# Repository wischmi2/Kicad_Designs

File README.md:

# Kicad_Designs

nRF54L15 sensor nodes (feather + one CN1 sensor board per node), the pouch gateway, and tools.
Layout since 2026-11-10 (old -> new map: `docs\reorg_2026-11-10.md`). Every board folder has a STATUS.md; read it first.

```
hardware\
  feather\              nRF54L15 feather, main board (KiCad project in feather\nrf54l15_feather\)
  sensors\              CN1 sensor boards + CN1_SENSOR_CONNECTOR.md, SENSORS.md (SENS_ID register)
    template\ ph\ orp\ dissolved_oxygen\ conductivity\ water_level\ water_level_tc2030\
  gateway\              pouch gateway (docs\ inside)
  prog_adapter\         programming adapter (XM125 UART, TC2030 SWD, USB-C 3.0 V)
  archive\              old/paused boards: nrf54l15_v2, v3, v4, ph_sensor, xiao_breakout,
                        pcbway_production, soil_moisture (the old root-level project)
firmware\
  boards\               Zephyr board definitions (firmware\ is BOARD_ROOT)
  apps\feather_node\    node application, build/flash scripts
mechanical\             enclosure exports: tidemark, ledger, crown, probe_nodes, bench_tray,
                        concepts\<product>, hardware_lists
docs\                   cross-board notes, datasheets, sourcing, cost analysis
CLAUDE.md               coordinator instructions and status log
```

Per board: `sourcing\` holds BOMs and part notes, `docs\` holds renders and design notes,
`archive\` / `fab_<date>\` hold fab output. KiCad project files keep their original names.
Board STEP and fab-zip handoffs live outside the repo in `C:\Personal-Agents\shared\handoff\<board>\`.

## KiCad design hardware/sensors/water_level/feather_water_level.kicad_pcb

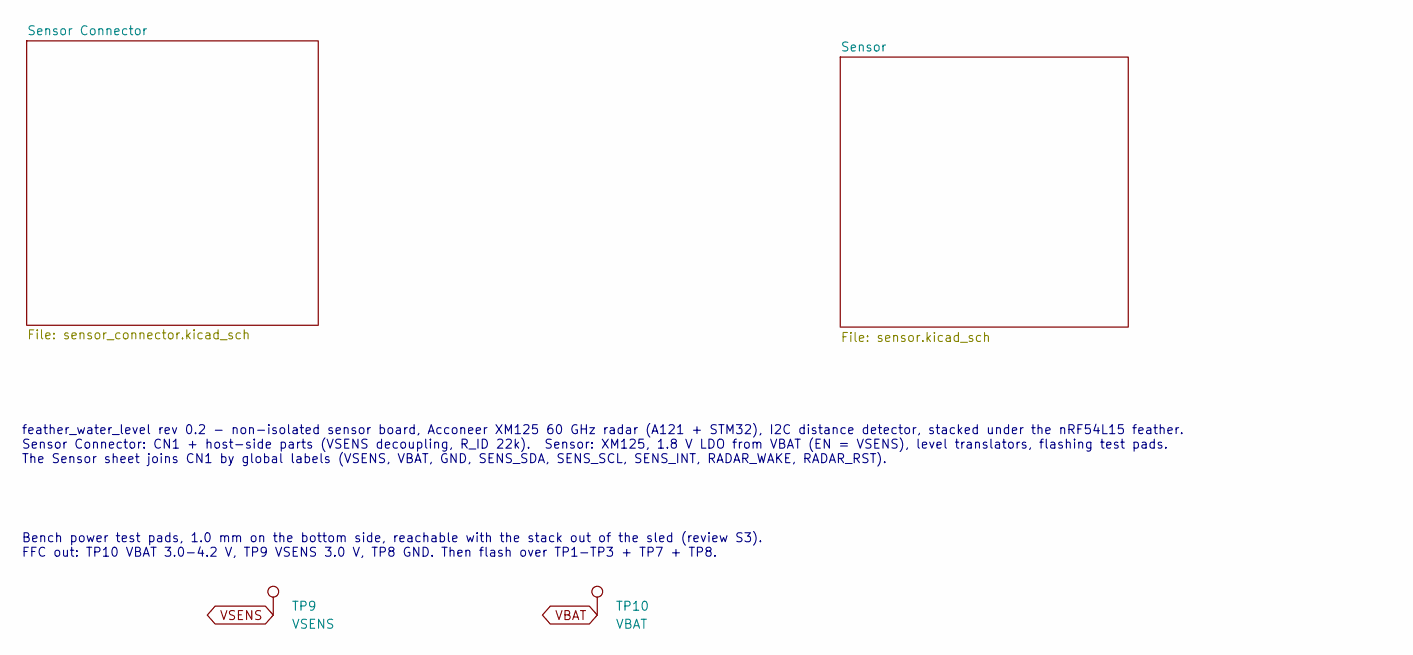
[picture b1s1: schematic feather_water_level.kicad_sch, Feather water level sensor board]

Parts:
TP9: VSENS; TestPoint_Pad_D1.0mm; MPN DNP (test pad)
TP10: VBAT; TestPoint_Pad_D1.0mm; MPN DNP (test pad)

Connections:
VBAT: TP10.1; also elsewhere on the board
VSENS: TP9.1; also elsewhere on the board

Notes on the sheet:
feather_water_level rev 0.2 - non-isolated sensor board, Acconeer XM125 60 GHz radar (A121 + STM32), I2C distance detector, stacked under the nRF54L15 feather. Sensor Connector: CN1 + host-side parts (VSENS decoupling, R_ID 22k). Sensor: XM125, 1.8 V LDO from VBAT (EN = VSENS), level translators, f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
Bench power test pads, 1.0 mm on the bottom side, reachable with the stack out of the sled (review S3). FFC out: TP10 VBAT 3.0-4.2 V, TP9 VSENS 3.0 V, TP8 GND. Then flash over TP1-TP3 + TP7 + TP8.

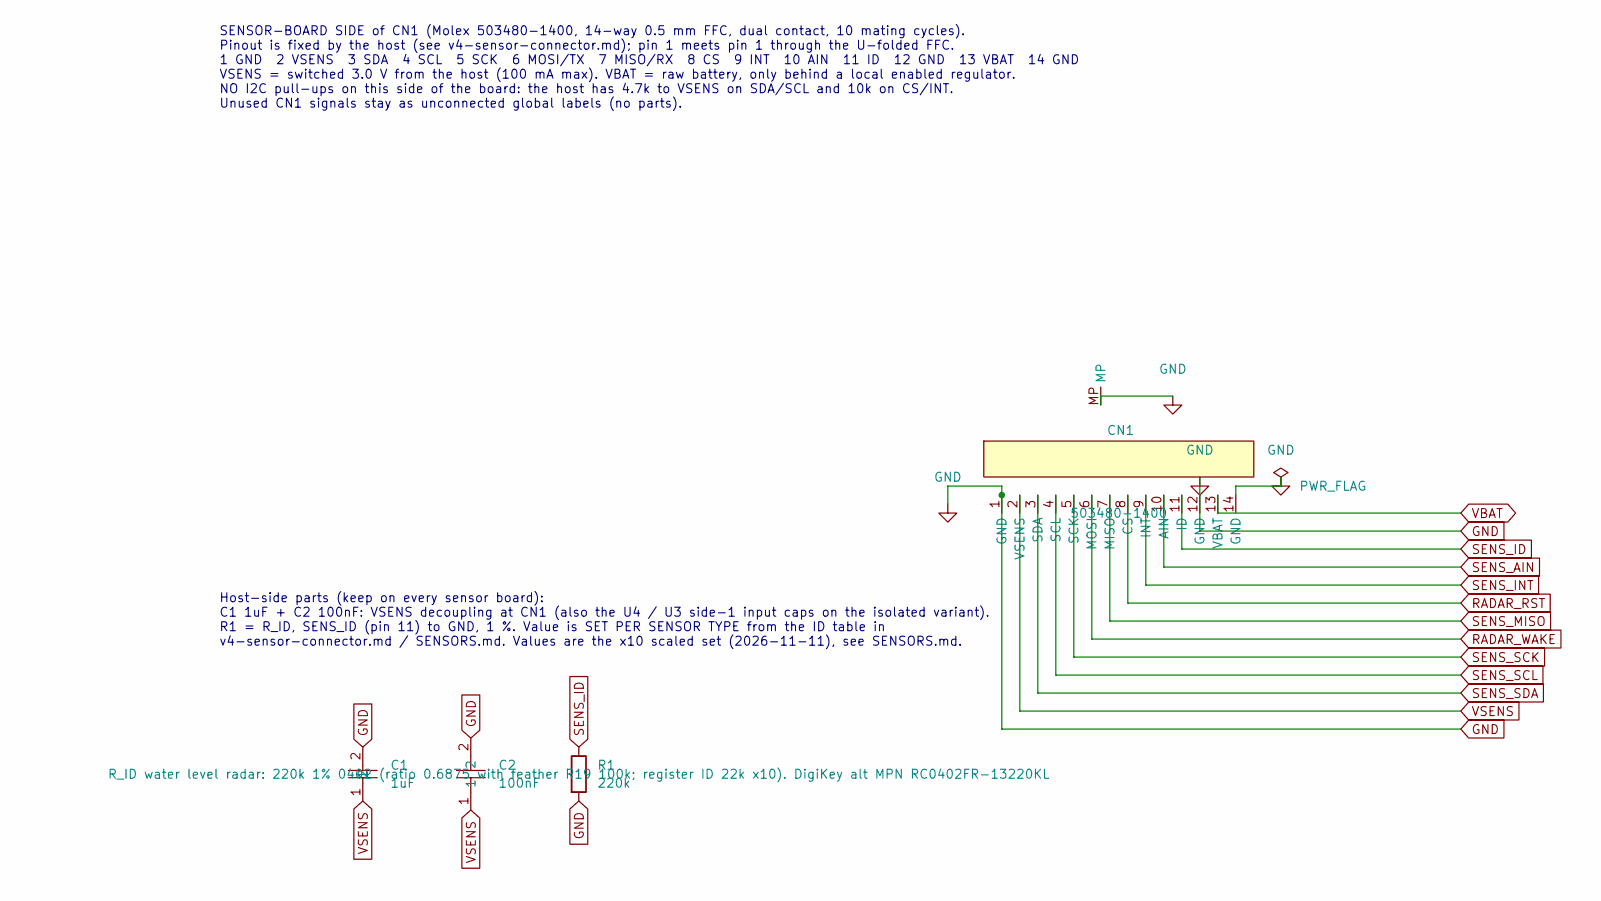
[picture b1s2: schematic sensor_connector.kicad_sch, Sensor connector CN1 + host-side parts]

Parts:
C1: 1uF; C0402; MPN CL05A105KO5NNNC; LCSC Part C29266
C2: 100nF; C0603; MPN CC0603KRX7R9BB104; LCSC Part C14663
CN1: 503480-1400; Molex_503480-1400_1x14-1MP_P0.50mm_Horizontal; MPN 503480-1400
R1: 220k; R0402; Tolerance 1%; MPN RC0402FR-07220KL

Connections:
GND: C1.2, C2.2, CN1.1 (GND), CN1.12 (GND), CN1.14 (GND), CN1.MP, R1.2; also elsewhere on the board
RADAR_RST: CN1.8 (CS); also elsewhere on the board
RADAR_WAKE: CN1.6 (MOSI); also elsewhere on the board
SENS_AIN: CN1.10 (AIN)
SENS_ID: CN1.11 (ID), R1.1
SENS_INT: CN1.9 (INT); also elsewhere on the board
SENS_MISO: CN1.7 (MISO)
SENS_SCK: CN1.5 (SCK)
SENS_SCL: CN1.4 (SCL); also elsewhere on the board
SENS_SDA: CN1.3 (SDA); also elsewhere on the board
VBAT: CN1.13 (VBAT); also elsewhere on the board
VSENS: C1.1, C2.1, CN1.2 (VSENS); also elsewhere on the board

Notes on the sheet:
SENSOR-BOARD SIDE of CN1 (Molex 503480-1400, 14-way 0.5 mm FFC, dual contact, 10 mating cycles). Pinout is fixed by the host (see v4-sensor-connector.md); pin 1 meets pin 1 through the U-folded FFC. 1 GND 2 VSENS 3 SDA 4 SCL 5 SCK 6 MOSI/TX 7 MISO/RX 8 CS 9 INT 10 AIN 11 ID 12 GND 13 VBAT 14 GND VS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
Host-side parts (keep on every sensor board): C1 1uF + C2 100nF: VSENS decoupling at CN1 (also the U4 / U3 side-1 input caps on the isolated variant). R1 = R_ID, SENS_ID (pin 11) to GND, 1 %. Value is SET PER SENSOR TYPE from the ID table in v4-sensor-connector.md / SENSORS.md. Values are the x10 s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

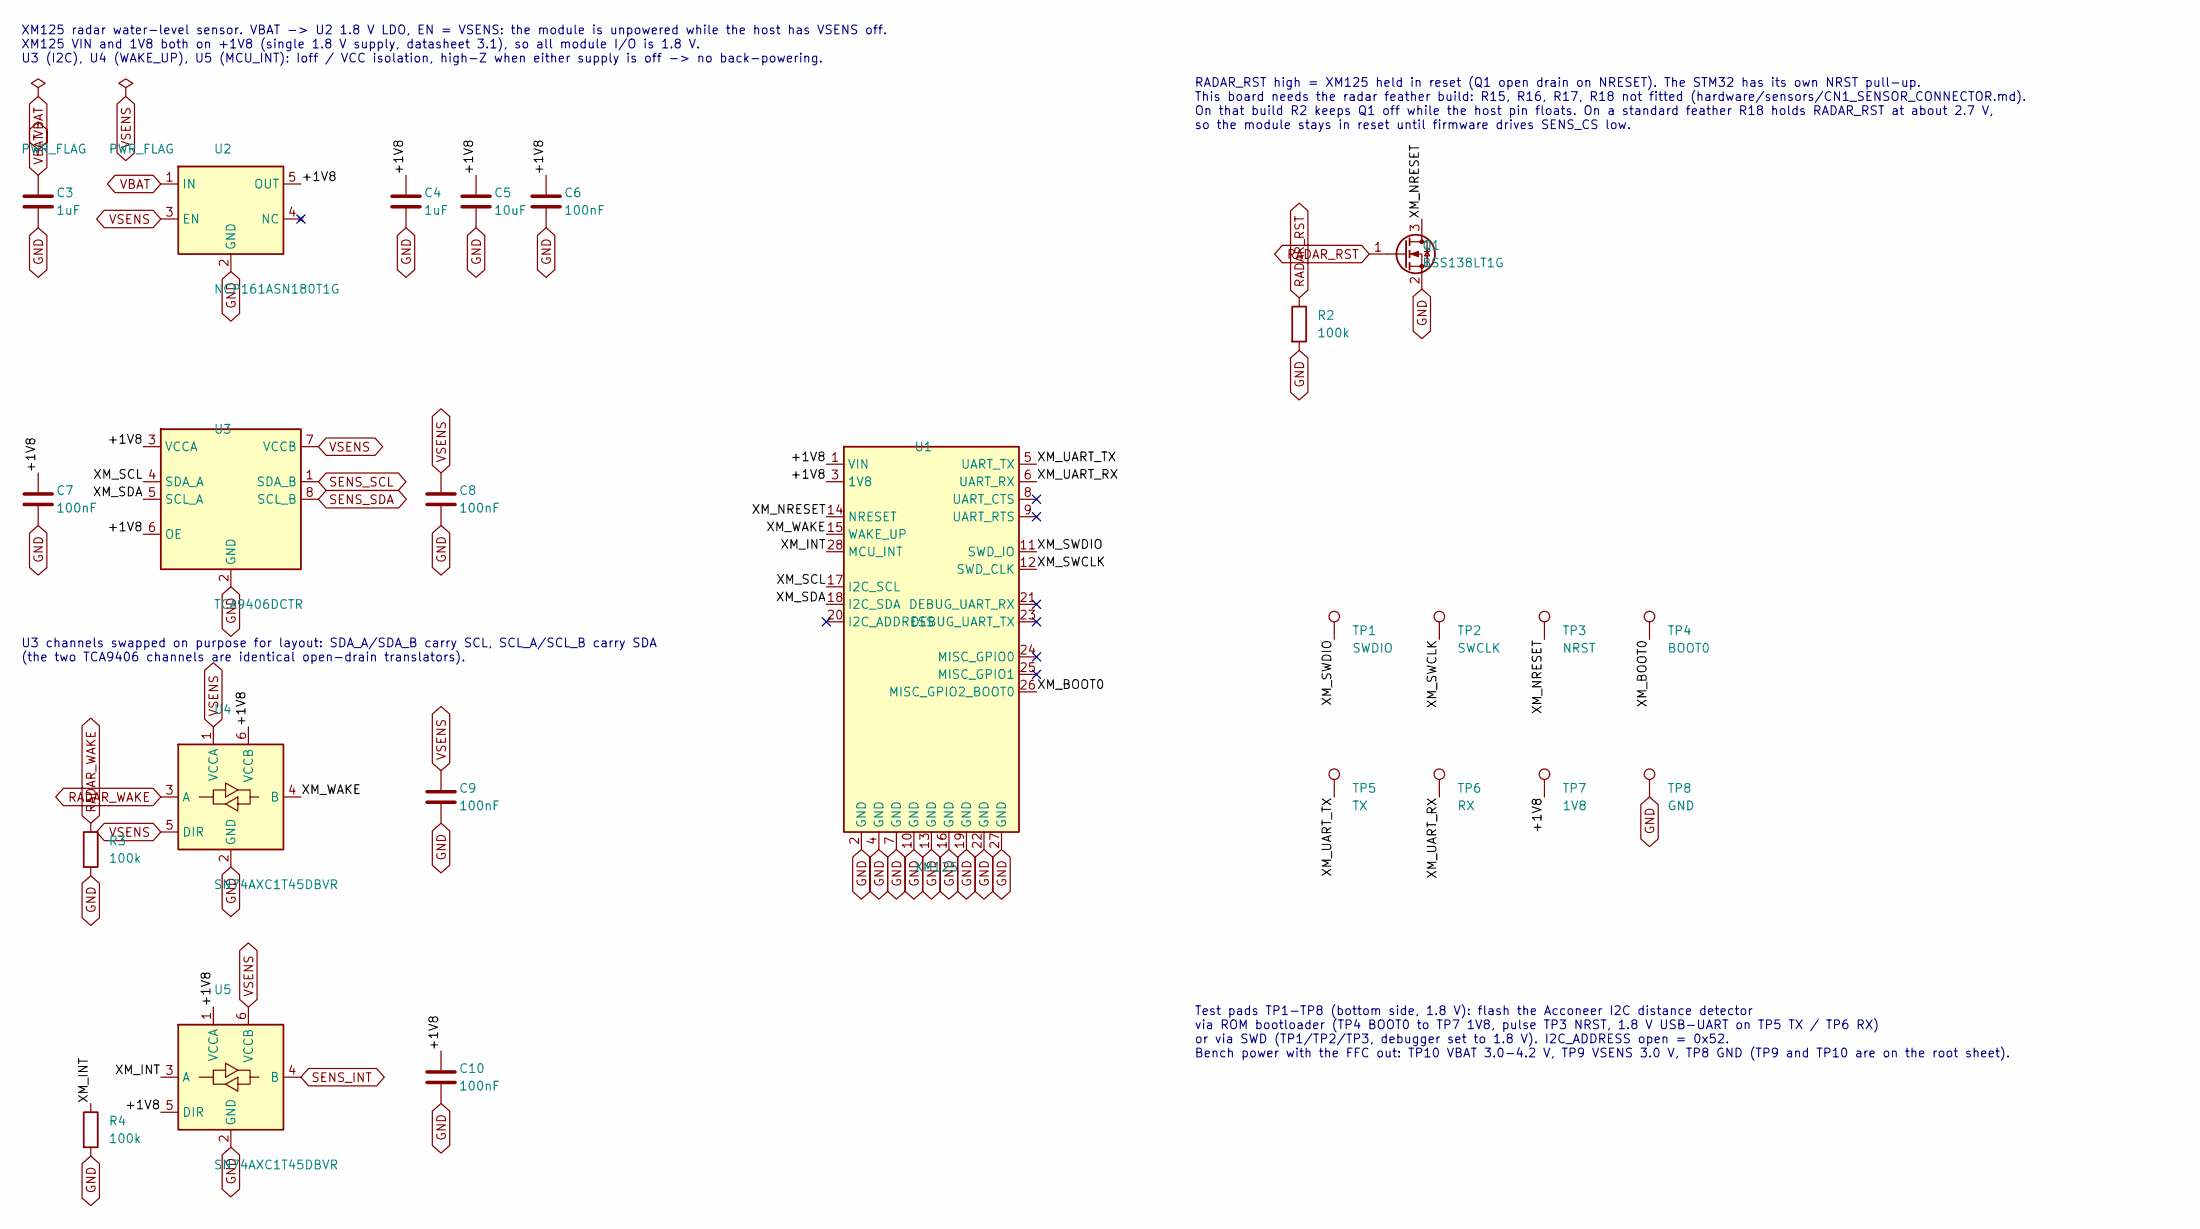
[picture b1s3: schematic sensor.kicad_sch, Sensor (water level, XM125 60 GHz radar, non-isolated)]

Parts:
C3, C4: 1uF; C_0402_1005Metric; Voltage 16V; MPN CL05A105KO5NNNC
C5: 10uF; C_0402_1005Metric; Voltage 6.3V; MPN GRM155R60J106ME15D
C6, C7, C8, C9, C10: 100nF; C_0402_1005Metric; Voltage 10V; MPN GRM155R71A104KA01D
Q1: BSS138LT1G; SOT-23; MPN BSS138LT1G
R2, R3, R4: 100k; R_0402_1005Metric; Tolerance 1%; MPN RC0402FR-07100KL
TP1: SWDIO; TestPoint_Pad_D1.0mm; MPN DNP (test pad)
TP2: SWCLK; TestPoint_Pad_D1.0mm; MPN DNP (test pad)
TP3: NRST; TestPoint_Pad_D1.0mm; MPN DNP (test pad)
TP4: BOOT0; TestPoint_Pad_D1.0mm; MPN DNP (test pad)
TP5: TX; TestPoint_Pad_D1.0mm; MPN DNP (test pad)
TP6: RX; TestPoint_Pad_D1.0mm; MPN DNP (test pad)
TP7: 1V8; TestPoint_Pad_D1.0mm; MPN DNP (test pad)
TP8: GND; TestPoint_Pad_D1.0mm; MPN DNP (test pad)
U1: XM125; Acconeer_XM125; MPN XM125
U2: NCP161ASN180T1G; SOT-23-5; MPN NCP161ASN180T1G
U3: TCA9406DCTR; SSOP-8_2.95x2.8mm_P0.65mm; MPN TCA9406DCTR
U4, U5: SN74AXC1T45DBVR; SOT-23-6; MPN SN74AXC1T45DBVR

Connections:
/Sensor/+1V8: C4.1, C5.1, C6.1, C7.1, C10.1, TP7.1, U1.1 (VIN), U1.3 (1V8), U2.5 (OUT), U3.3 (VCCA), U3.6 (OE), U4.6 (VCCB), U5.1 (VCCA), U5.5 (DIR)
/Sensor/XM_BOOT0: TP4.1, U1.26 (MISC_GPIO2_BOOT0)
/Sensor/XM_INT: R4.1, U1.28 (MCU_INT), U5.3 (A)
/Sensor/XM_NRESET: Q1.3 (D), TP3.1, U1.14 (NRESET)
/Sensor/XM_SCL: U1.17 (I2C_SCL), U3.4 (SDA_A)
/Sensor/XM_SDA: U1.18 (I2C_SDA), U3.5 (SCL_A)
/Sensor/XM_SWCLK: TP2.1, U1.12 (SWD_CLK)
/Sensor/XM_SWDIO: TP1.1, U1.11 (SWD_IO)
/Sensor/XM_UART_RX: TP6.1, U1.6 (UART_RX)
/Sensor/XM_UART_TX: TP5.1, U1.5 (UART_TX)
/Sensor/XM_WAKE: U1.15 (WAKE_UP), U4.4 (B)
GND: C3.2, C4.2, C5.2, C6.2, C7.2, C8.2, C9.2, C10.2, Q1.2 (S), R2.2, R3.2, R4.2, TP8.1, U1.2 (GND), U1.4 (GND), U1.7 (GND), U1.10 (GND), U1.13 (GND), U1.16 (GND), U1.19 (GND), U1.22 (GND), U1.27 (GND), U2.2 (GND), U3.2 (GND), U4.2 (GND), U5.2 (GND); also elsewhere on the board
RADAR_RST: Q1.1 (G), R2.1; also elsewhere on the board
RADAR_WAKE: R3.1, U4.3 (A); also elsewhere on the board
SENS_INT: U5.4 (B); also elsewhere on the board
SENS_SCL: U3.1 (SDA_B); also elsewhere on the board
SENS_SDA: U3.8 (SCL_B); also elsewhere on the board
VBAT: C3.1, U2.1 (IN); also elsewhere on the board
VSENS: C8.1, C9.1, U2.3 (EN), U3.7 (VCCB), U4.1 (VCCA), U4.5 (DIR), U5.6 (VCCB); also elsewhere on the board

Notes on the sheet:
XM125 radar water-level sensor. VBAT -> U2 1.8 V LDO, EN = VSENS: the module is unpowered while the host has VSENS off. XM125 VIN and 1V8 both on +1V8 (single 1.8 V supply, datasheet 3.1), so all module I/O is 1.8 V. U3 (I2C), U4 (WAKE_UP), U5 (MCU_INT): Ioff / VCC isolation, high-Z when either sup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
U3 channels swapped on purpose for layout: SDA_A/SDA_B carry SCL, SCL_A/SCL_B carry SDA (the two TCA9406 channels are identical open-drain translators).
RADAR_RST high = XM125 held in reset (Q1 open drain on NRESET). The STM32 has its own NRST pull-up. This board needs the radar feather build: R15, R16, R17, R18 not fitted (hardware/sensors/CN1_SENSOR_CONNECTOR.md). On that build R2 keeps Q1 off while the host pin floats. On a standard feather R18 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
Test pads TP1-TP8 (bottom side, 1.8 V): flash the Acconeer I2C distance detector via ROM bootloader (TP4 BOOT0 to TP7 1V8, pulse TP3 NRST, 1.8 V USB-UART on TP5 TX / TP6 RX) or via SWD (TP1/TP2/TP3, debugger set to 1.8 V). I2C_ADDRESS open = 0x52. Bench power with the FFC out: TP10 VBAT 3.0-4.2 V, 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

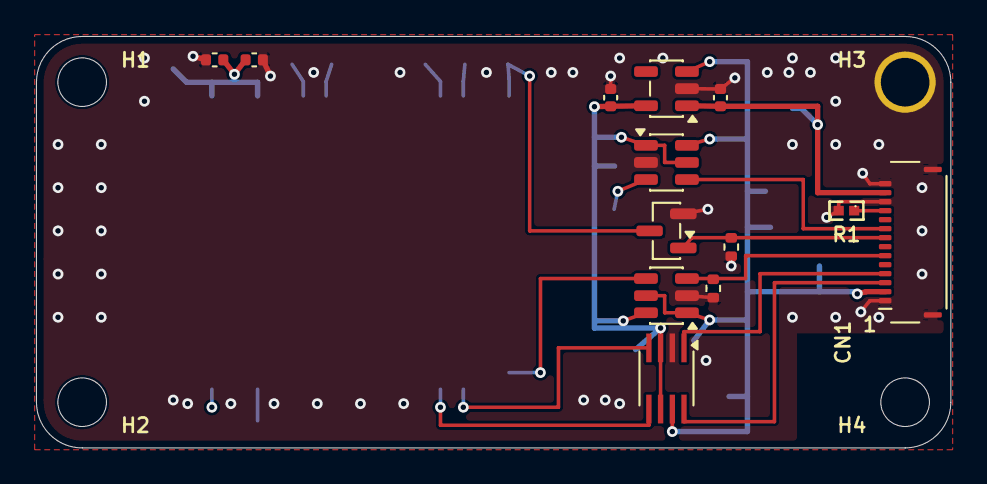
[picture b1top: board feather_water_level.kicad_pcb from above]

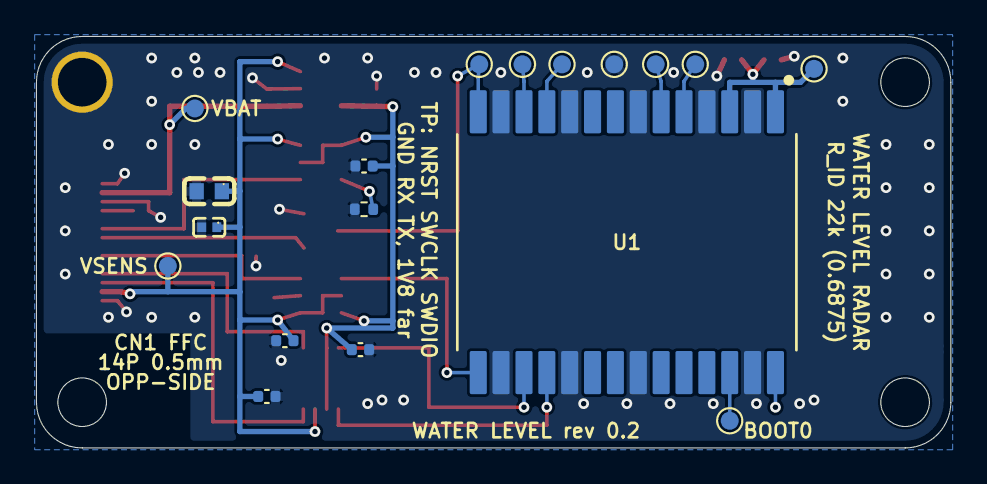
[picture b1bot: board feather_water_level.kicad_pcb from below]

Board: 4 copper layers, 50.8 x 22.9 mm, 35 parts (18 on the bottom side), 20 nets.

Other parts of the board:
H1, H2, H4: M2.5 2.7mm NPTH; MountingHole_2.5mm
H3: M2.5 2.7mm PTH GND; MountingHole_2.5mm_Pad

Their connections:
GND: H3.1; also elsewhere on the board

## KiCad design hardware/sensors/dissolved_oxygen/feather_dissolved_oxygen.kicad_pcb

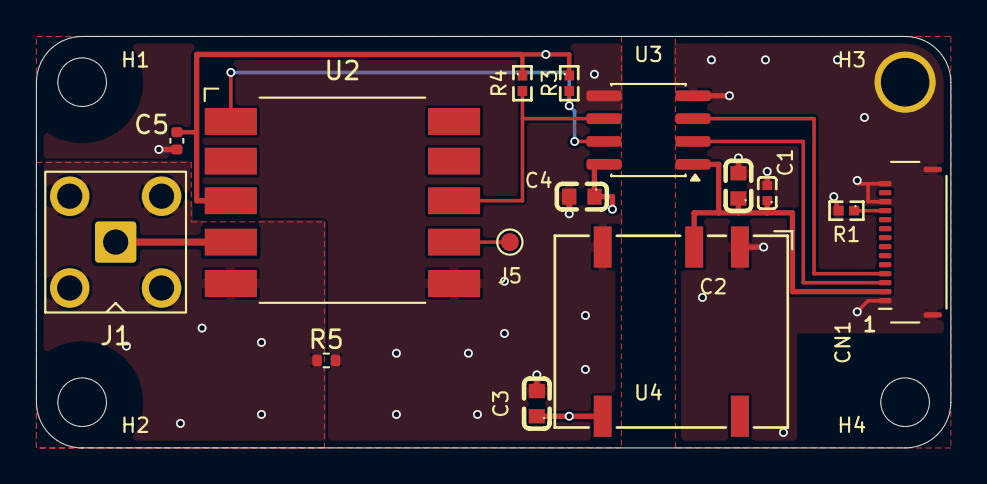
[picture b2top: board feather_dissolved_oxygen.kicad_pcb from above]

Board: 4 copper layers, 50.8 x 22.9 mm, 19 parts (0 on the bottom side), 12 nets.

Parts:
C1: 1uF; C0402
C2, C4: 100nF; C0603
C3: 2.2uF; C0603
C5: 1uF; C_0402_1005Metric
CN1: 503480-1400; Molex_503480-1400_1x14-1MP_P0.50mm_Horizontal
H1, H2, H4: M2.5 2.7mm NPTH; MountingHole_2.5mm
H3: M2.5 2.7mm PTH GND; MountingHole_2.5mm_Pad
J1: SMA BWSMA-KWE-Z001; SMA_BAT_Wireless_BWSMA-KWE-Z001
J5: Conn_01x01; TestPoint_Pad_D1.0mm
R1: 22k; R0402
R3, R4: 4.7k; R0402
R5: 0R DNP; R_0402_1005Metric
U2: Atlas_DO_OEM
U3: ADuM1250; SOIC-8_3.9x4.9mm_P1.27mm
U4: NXE1S0303MC; Converter_DCDC_Murata_NXExSxxxxMC_SMD

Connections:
/Sensor/DO_PRB: J1.1, U2.4
/Sensor/DO_PRB_GND: J1.2, R5.1, U2.5
GND: C1.2, C2.2, CN1.1 (GND), CN1.12 (GND), CN1.14 (GND), CN1.MP, H3.1, R1.2, U3.4 (GND1), U4.1 (-Vin)
GND_ISO: C3.2, C4.2, C5.2, R5.2, U2.6, U3.5 (GND2), U4.7 (-Vout)
INT_ISO: J5.1 (Pin_1_1), U2.7
SCL_ISO: R4.2, U2.8, U3.6 (SCL2)
SDA_ISO: R3.2, U2.1, U3.7 (SDA2)
SENS_ID: CN1.11 (ID), R1.1
SENS_SCL: CN1.4 (SCL), U3.3 (SCL1)
SENS_SDA: CN1.3 (SDA), U3.2 (SDA1)
VDD_ISO: C3.1, C4.1, C5.1, R3.1, R4.1, U2.3, U3.8 (VDD2), U4.8 (+Vout)
VSENS: C1.1, C2.1, CN1.2 (VSENS), U3.1 (VDD1), U4.3 (+Vin)

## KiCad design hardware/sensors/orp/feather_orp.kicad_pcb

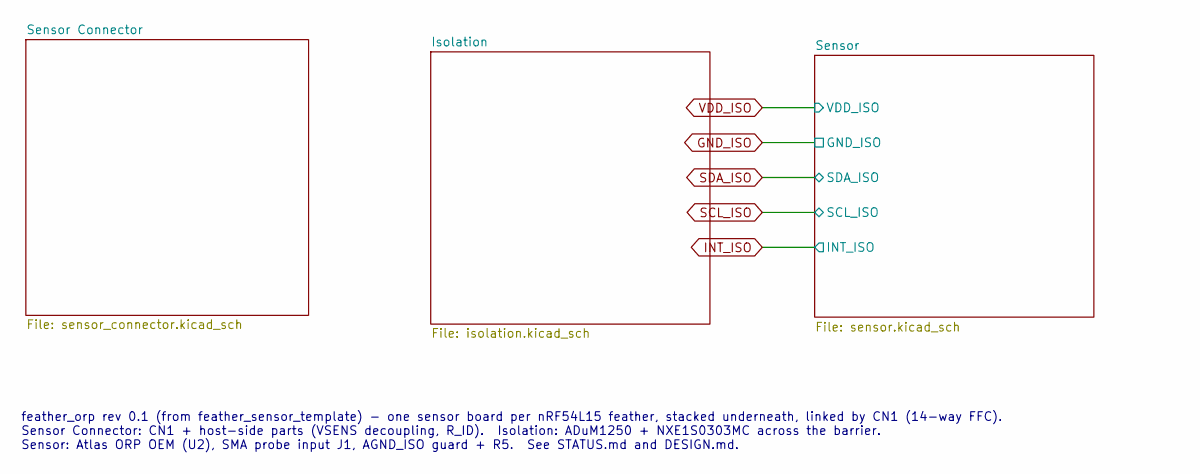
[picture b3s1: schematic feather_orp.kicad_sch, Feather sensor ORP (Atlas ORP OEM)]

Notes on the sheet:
feather_orp rev 0.1 (from feather_sensor_template) - one sensor board per nRF54L15 feather, stacked underneath, linked by CN1 (14-way FFC). Sensor Connector: CN1 + host-side parts (VSENS decoupling, R_ID). Isolation: ADuM1250 + NXE1S0303MC across the barrier. Sensor: Atlas ORP OEM (U2), SMA probe i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

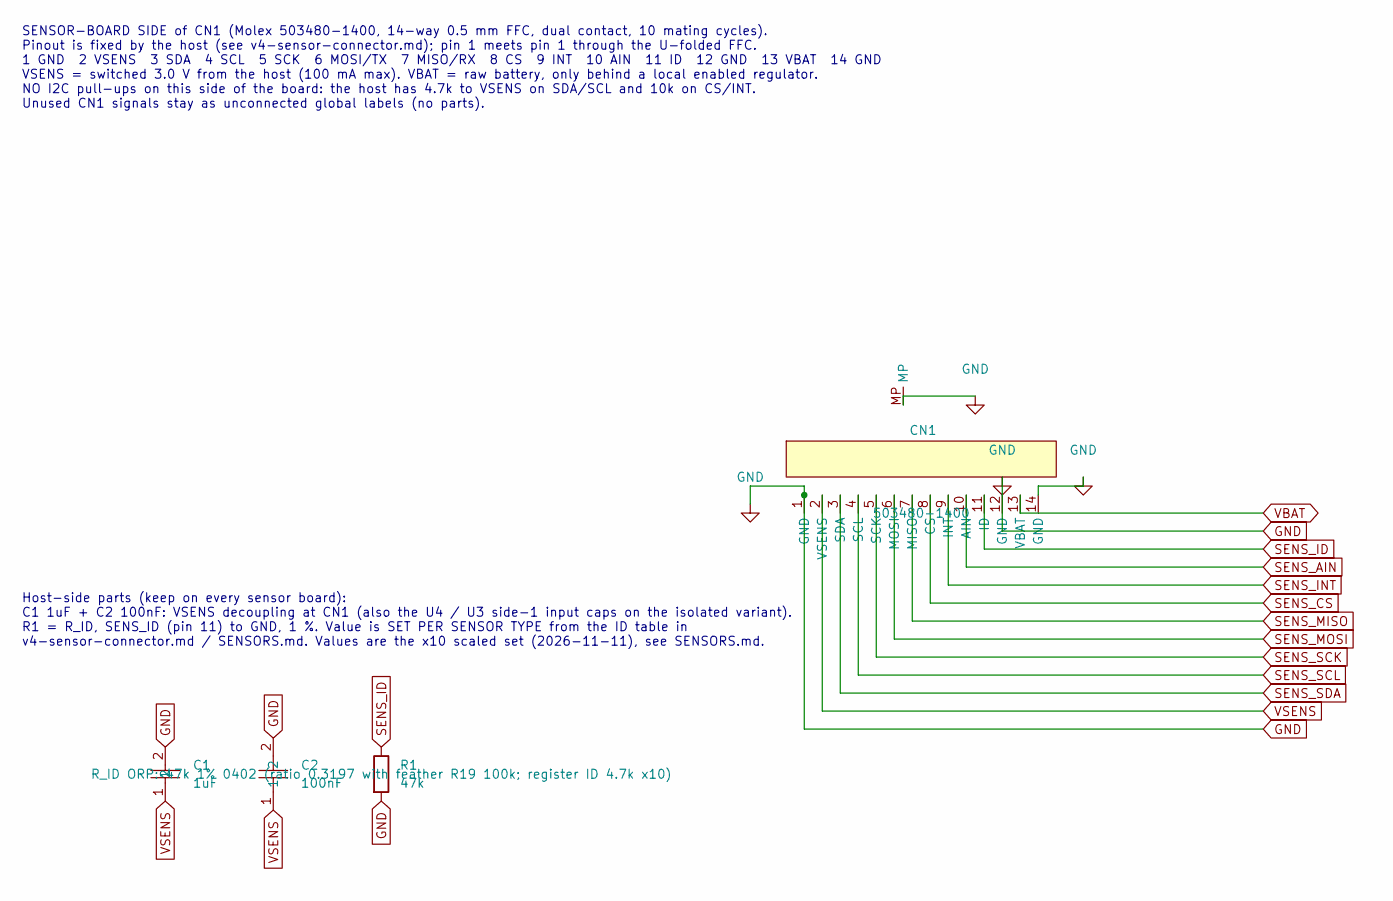
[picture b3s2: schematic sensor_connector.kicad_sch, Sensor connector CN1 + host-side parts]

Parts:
C1: 1uF; C0402; MPN CL05A105KO5NNNC; LCSC Part C29266
C2: 100nF; C0603; MPN CC0603KRX7R9BB104; LCSC Part C14663
CN1: 503480-1400; Molex_503480-1400_1x14-1MP_P0.50mm_Horizontal; MPN 503480-1400
R1: 47k; R0402; Tolerance 1%; MPN RC0402FR-0747KL

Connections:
GND: C1.2, C2.2, CN1.1 (GND), CN1.12 (GND), CN1.14 (GND), CN1.MP, R1.2; also elsewhere on the board
SENS_AIN: CN1.10 (AIN)
SENS_CS: CN1.8 (CS)
SENS_ID: CN1.11 (ID), R1.1
SENS_INT: CN1.9 (INT)
SENS_MISO: CN1.7 (MISO)
SENS_MOSI: CN1.6 (MOSI)
SENS_SCK: CN1.5 (SCK)
SENS_SCL: CN1.4 (SCL); also elsewhere on the board
SENS_SDA: CN1.3 (SDA); also elsewhere on the board
VBAT: CN1.13 (VBAT)
VSENS: C1.1, C2.1, CN1.2 (VSENS); also elsewhere on the board

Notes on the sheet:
SENSOR-BOARD SIDE of CN1 (Molex 503480-1400, 14-way 0.5 mm FFC, dual contact, 10 mating cycles). Pinout is fixed by the host (see v4-sensor-connector.md); pin 1 meets pin 1 through the U-folded FFC. 1 GND 2 VSENS 3 SDA 4 SCL 5 SCK 6 MOSI/TX 7 MISO/RX 8 CS 9 INT 10 AIN 11 ID 12 GND 13 VBAT 14 GND VS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
Host-side parts (keep on every sensor board): C1 1uF + C2 100nF: VSENS decoupling at CN1 (also the U4 / U3 side-1 input caps on the isolated variant). R1 = R_ID, SENS_ID (pin 11) to GND, 1 %. Value is SET PER SENSOR TYPE from the ID table in v4-sensor-connector.md / SENSORS.md. Values are the x10 s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

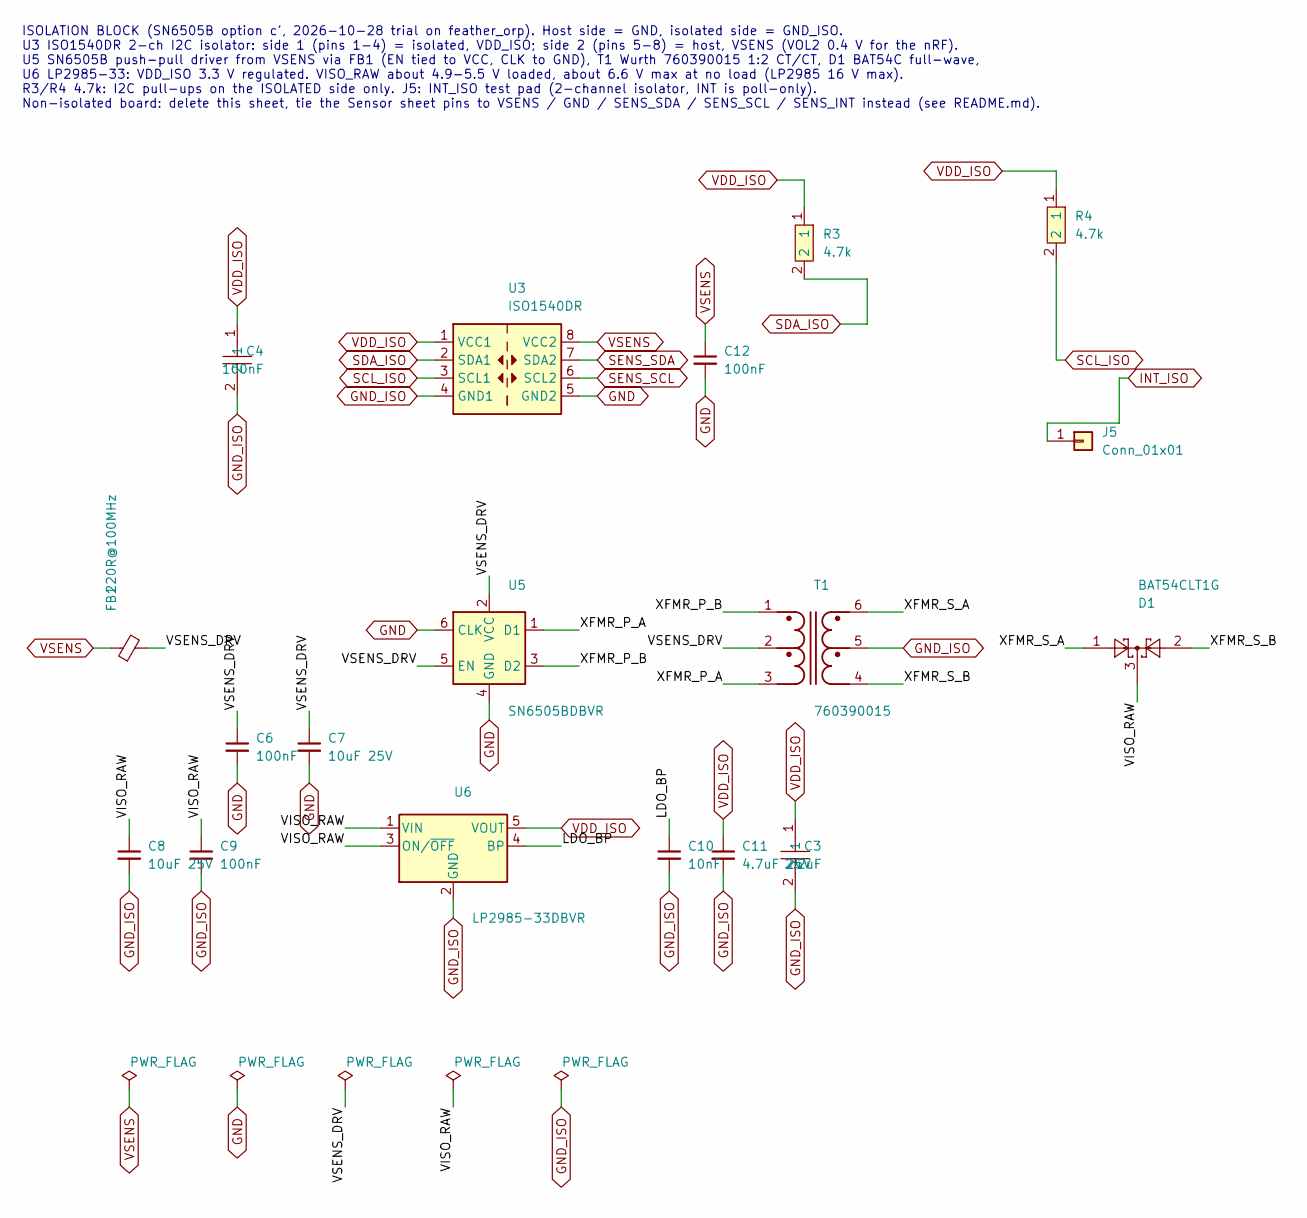
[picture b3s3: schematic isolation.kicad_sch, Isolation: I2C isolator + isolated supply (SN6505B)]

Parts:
C3: 2.2uF; C0603; MPN GRM188R71A225KE15D; LCSC Part C86018
C4: 100nF; C0603; MPN CC0603KRX7R9BB104; LCSC Part C14663
C6, C9, C12: 100nF; C_0402_1005Metric; MPN GRM155R71C104KA88D
C7, C8: 10uF 25V; C_0805_2012Metric; MPN GRM21BR61E106MA73L
C10: 10nF; C_0402_1005Metric; MPN GRM155R71H103KA88D
C11: 4.7uF 25V; C_0603_1608Metric; MPN GRM188R61E475KE11D
D1: BAT54CLT1G; SOT-23; MPN BAT54CLT1G
FB1: 220R@100MHz; L_0603_1608Metric; MPN BLM18PG221SN1D
J5: Conn_01x01; TestPoint_Pad_D1.0mm
R3, R4: 4.7k; R0402; MPN CRCW04024K70FKED; LCSC Part C482193
T1: 760390015; WE-PPTI_760390015; MPN 760390015
U3: ISO1540DR; SOIC-8_3.9x4.9mm_P1.27mm; MPN ISO1540DR
U5: SN6505BDBVR; SOT-23-6; MPN SN6505BDBVR
U6: LP2985-33DBVR; SOT-23-5; MPN LP2985-33DBVR

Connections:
/Isolation/LDO_BP: C10.1, U6.4 (BP)
/Isolation/VISO_RAW: C8.1, C9.1, D1.3, U6.1 (VIN), U6.3 (ON/~OFF)
/Isolation/VSENS_DRV: C6.1, C7.1, FB1.2, T1.2 (P_CT), U5.2 (VCC), U5.5 (EN)
/Isolation/XFMR_P_A: T1.3 (P_B), U5.1 (D1)
/Isolation/XFMR_P_B: T1.1 (P_A), U5.3 (D2)
/Isolation/XFMR_S_A: D1.1, T1.6 (S_A)
/Isolation/XFMR_S_B: D1.2, T1.4 (S_B)
GND: C6.2, C7.2, C12.2, U3.5 (GND2), U5.4 (GND), U5.6 (CLK); also elsewhere on the board
GND_ISO: C3.2, C4.2, C8.2, C9.2, C10.2, C11.2, T1.5 (S_CT), U3.4 (GND1), U6.2 (GND); also elsewhere on the board
INT_ISO: J5.1 (Pin_1_1); also elsewhere on the board
SCL_ISO: R4.2, U3.3 (SCL1); also elsewhere on the board
SDA_ISO: R3.2, U3.2 (SDA1); also elsewhere on the board
SENS_SCL: U3.6 (SCL2); also elsewhere on the board
SENS_SDA: U3.7 (SDA2); also elsewhere on the board
VDD_ISO: C3.1, C4.1, C11.1, R3.1, R4.1, U3.1 (VDD1), U6.5 (VOUT); also elsewhere on the board
VSENS: C12.1, FB1.1, U3.8 (VDD2); also elsewhere on the board

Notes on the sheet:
ISOLATION BLOCK (SN6505B option c', 2026-10-28 trial on feather_orp). Host side = GND, isolated side = GND_ISO. U3 ISO1540DR 2-ch I2C isolator: side 1 (pins 1-4) = isolated, VDD_ISO; side 2 (pins 5-8) = host, VSENS (VOL2 0.4 V for the nRF). U5 SN6505B push-pull driver from VSENS via FB1 (EN tied to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

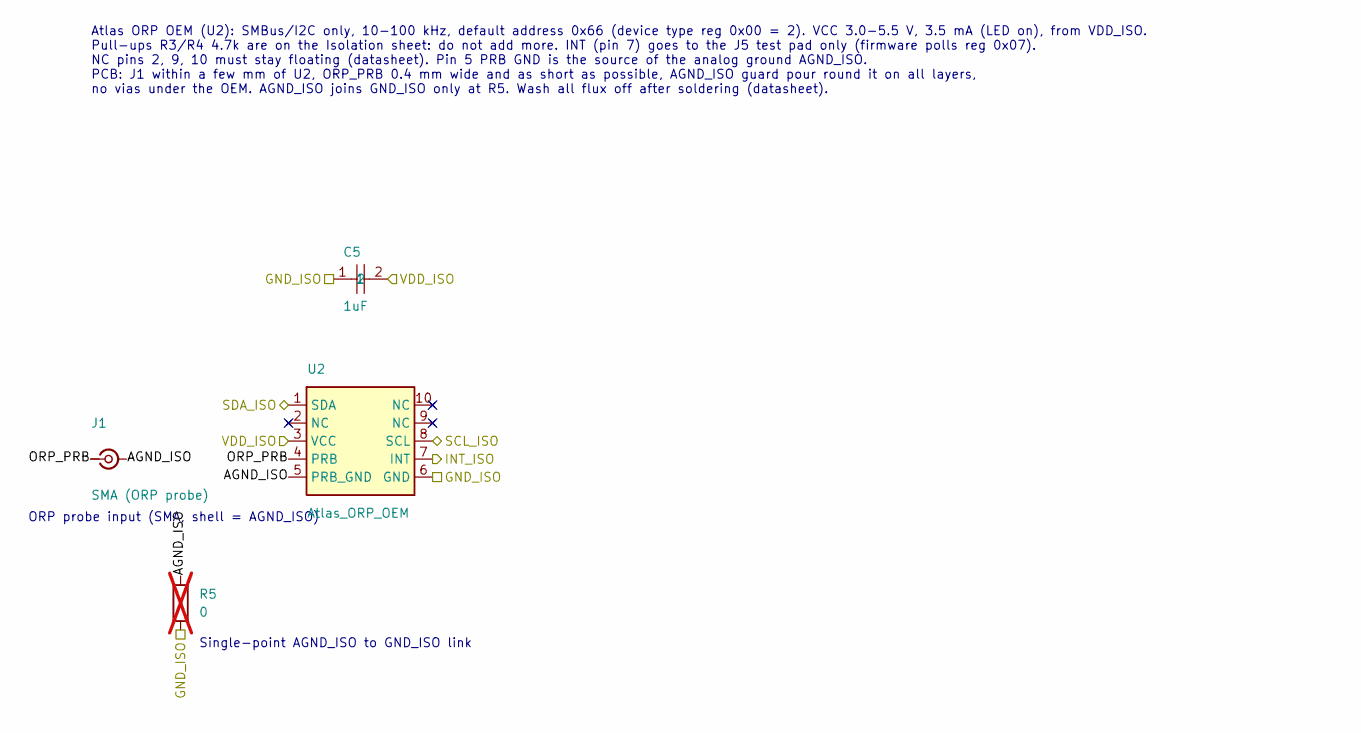
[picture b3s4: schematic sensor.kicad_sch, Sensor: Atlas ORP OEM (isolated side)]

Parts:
C5: 1uF; C0402; MPN CL05A105KO5NNNC; LCSC Part C29266
J1: SMA (ORP probe); SMA_BAT_Wireless_BWSMA-KWE-Z001; MPN BWSMA-KWE-Z001; LCSC Part C496551
R5: 0; R0402; MPN ERJ-2GE0R00X; not fitted
U2: Atlas_ORP_OEM; MPN OEM-ORP

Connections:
/Sensor/AGND_ISO: J1.2 (Ext), R5.1, U2.5 (PRB_GND)
/Sensor/ORP_PRB: J1.1 (In), U2.4 (PRB)
GND_ISO: C5.1, R5.2, U2.6 (GND); also elsewhere on the board
INT_ISO: U2.7 (INT); also elsewhere on the board
SCL_ISO: U2.8 (SCL); also elsewhere on the board
SDA_ISO: U2.1 (SDA); also elsewhere on the board
VDD_ISO: C5.2, U2.3 (VCC); also elsewhere on the board

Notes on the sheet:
Atlas ORP OEM (U2): SMBus/I2C only, 10-100 kHz, default address 0x66 (device type reg 0x00 = 2). VCC 3.0-5.5 V, 3.5 mA (LED on), from VDD_ISO. Pull-ups R3/R4 4.7k are on the Isolation sheet: do not add more. INT (pin 7) goes to the J5 test pad only (firmware polls reg 0x07). NC pins 2, 9, 10 must s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
ORP probe input (SMA, shell = AGND_ISO)
Single-point AGND_ISO to GND_ISO link

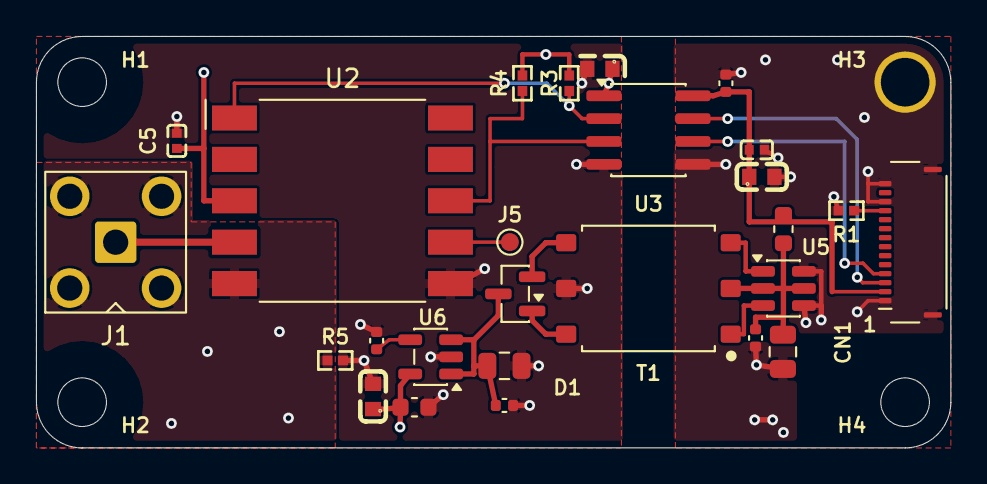
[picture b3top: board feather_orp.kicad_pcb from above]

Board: 4 copper layers, 50.8 x 22.9 mm, 30 parts (0 on the bottom side), 19 nets.

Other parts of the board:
H1, H2, H4: M2.5 2.7mm NPTH; MountingHole_2.5mm
H3: M2.5 2.7mm PTH GND; MountingHole_2.5mm_Pad

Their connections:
GND: H3.1; also elsewhere on the board

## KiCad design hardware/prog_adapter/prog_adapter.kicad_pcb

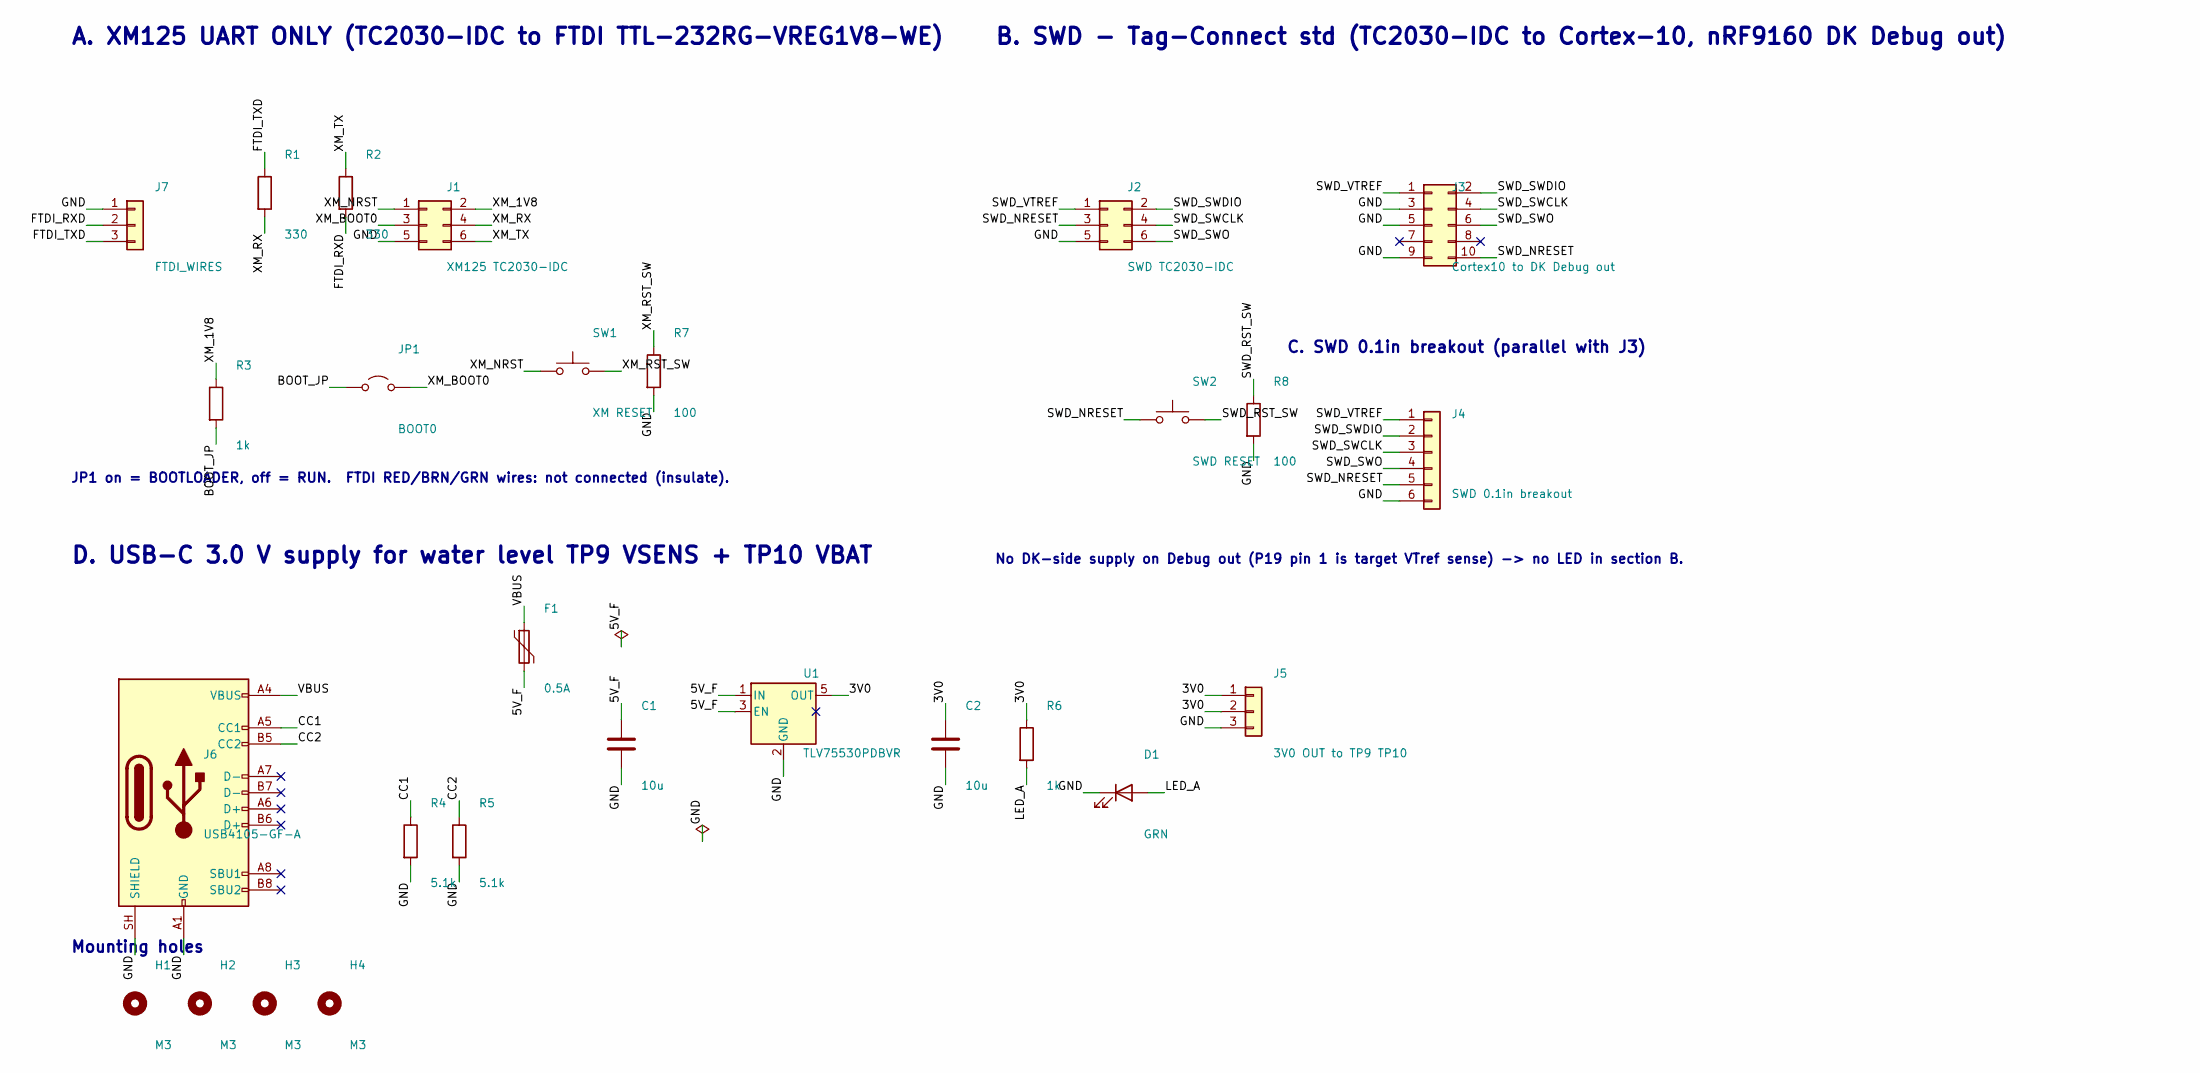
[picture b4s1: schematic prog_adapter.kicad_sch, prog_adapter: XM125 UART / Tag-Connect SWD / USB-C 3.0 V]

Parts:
C1, C2: 10u; C_0805_2012Metric; MPN CC0805KKX5R8BB106; DigiKey 311-1869-1-ND
D1: GRN; LED_0805_2012Metric; MPN LTST-C171GKT; DigiKey 160-1423-1-ND
F1: 0.5A; Fuse_1206_3216Metric; MPN MF-NSMF050-2; DigiKey MF-NSMF050-2CT-ND
H1, H2, H3, H4: M3; MountingHole_3.2mm_M3
J1: XM125 TC2030-IDC; BoxHeader_SSK05-BH-254-B3_2x03_P2.54mm_Vertical; MPN SSK05-BH-254-B3; DigiKey 2223-SSK05-BH-254-B3-ND
J2: SWD TC2030-IDC; BoxHeader_SSK05-BH-254-B3_2x03_P2.54mm_Vertical; MPN SSK05-BH-254-B3; DigiKey 2223-SSK05-BH-254-B3-ND
J3: Cortex10 to DK Debug out; BoxHeader_CNC_3220-10-0100-00_2x05_P1.27mm_Vertical; MPN 3220-10-0100-00; DigiKey 1175-1627-ND
J4: SWD 0.1in breakout; PinHeader_1x06_P2.54mm_Vertical; MPN PEC06SAAN; DigiKey 35-PEC06SAAN-ND
J5: 3V0 OUT to TP9 TP10; PinHeader_1x03_P2.54mm_Vertical; MPN PEC03SAAN; DigiKey 35-PEC03SAAN-ND
J6: USB4105-GF-A; USB_C_Receptacle_GCT_USB4105-xx-A_16P_TopMnt_Horizontal; MPN USB4105-GF-A; DigiKey 2073-USB4105-GF-ACT-ND
J7: FTDI_WIRES; FTDI_WirePads_3x_D1.0mm_ZipTie
JP1: BOOT0; PinHeader_1x02_P2.54mm_Vertical; MPN PEC02SAAN; DigiKey 35-PEC02SAAN-ND
R1, R2: 330; R_0805_2012Metric; MPN RC0805FR-07330RL; DigiKey 311-330CRCT-ND
R3, R6: 1k; R_0805_2012Metric; MPN RC0805FR-071KL; DigiKey 311-1.00KCRCT-ND
R4, R5: 5.1k; R_0805_2012Metric; MPN RC0805FR-075K1L; DigiKey 311-5.10KCRCT-ND
R7, R8: 100; R_0805_2012Metric; MPN RC0805FR-07100RL; DigiKey 311-100CRCT-ND
SW1: XM RESET; SW_PUSH_6mm; MPN B3F-1000; DigiKey SW400-ND
SW2: SWD RESET; SW_PUSH_6mm; MPN B3F-1000; DigiKey SW400-ND
U1: TLV75530PDBVR; SOT-23-5; MPN TLV75530PDBVR; DigiKey 296-TLV75530PDBVRCT-ND

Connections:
/3V0: C2.1, J5.1, J5.2, R6.1, U1.5 (OUT)
/5V_F: C1.1, F1.2, U1.1 (IN), U1.3 (EN)
/BOOT_JP: JP1.1 (A), R3.2
/CC1: J6.A5 (CC1), R4.1
/CC2: J6.B5 (CC2), R5.1
/FTDI_RXD: J7.2, R2.2
/FTDI_TXD: J7.3, R1.1
/GND: C1.2, C2.2, D1.1 (K), J1.5, J2.5, J3.3, J3.5, J3.9, J4.6, J5.3, J6.A1 (GND), J6.A12 (GND), J6.B1 (GND), J6.B12 (GND), J6.SH (SHIELD), J7.1, R4.2, R5.2, R7.2, R8.2, U1.2 (GND)
/LED_A: D1.2 (A), R6.2
/SWD_NRESET: J2.3, J3.10, J4.5, SW2.1
/SWD_RST_SW: R8.1, SW2.2
/SWD_SWCLK: J2.4, J3.4, J4.3
/SWD_SWDIO: J2.2, J3.2, J4.2
/SWD_SWO: J2.6, J3.6, J4.4
/SWD_VTREF: J2.1, J3.1, J4.1
/VBUS: F1.1, J6.A4 (VBUS), J6.A9 (VBUS), J6.B4 (VBUS), J6.B9 (VBUS)
/XM_1V8: J1.2, R3.1
/XM_BOOT0: J1.3, JP1.2 (B)
/XM_NRST: J1.1, SW1.1
/XM_RST_SW: R7.1, SW1.2
/XM_RX: J1.4, R1.2
/XM_TX: J1.6, R2.1

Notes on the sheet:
A. XM125 UART ONLY (TC2030-IDC to FTDI TTL-232RG-VREG1V8-WE)
B. SWD - Tag-Connect std (TC2030-IDC to Cortex-10, nRF9160 DK Debug out)
C. SWD 0.1in breakout (parallel with J3)
D. USB-C 3.0 V supply for water level TP9 VSENS + TP10 VBAT
JP1 on = BOOTLOADER, off = RUN. FTDI RED/BRN/GRN wires: not connected (insulate).
No DK-side supply on Debug out (P19 pin 1 is target VTref sense) -> no LED in section B.
Mounting holes
